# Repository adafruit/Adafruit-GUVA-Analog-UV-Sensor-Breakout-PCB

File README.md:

# Adafruit-GUVA-Analog-UV-Sensor-Breakout-PCB

__Format is EagleCAD schematic and board layout__

<a href="http://www.adafruit.com/products/1918"><br/>Click here to purchase one from the Adafruit shop</a>

Extend your light-sensing spectrum with this analog UV sensor module. It uses a UV photodiode, which can detect the 240-370nm range of light (which covers UVB and most of UVA spectrum). The signal level from the photodiode is very small, in the nano-ampere level, so we tossed on an opamp to amplify the signal to a more manageable volt-level.

This sensor is much simpler than our Si1145 breakout, it only does one thing and gives an analog voltage output instead of requiring a complicated I2C setup procedure. This makes it better for simple projects. It also has a 'true' UV sensor instead of a calibrated light-sensor. To use, power the sensor and op-amp by connecting V+ to 2.7-5.5VDC and GND to power ground. Then read the analog signal from the OUT pin. The output voltage is: Vo = 4.3 * Diode-Current-in-uA. So if the photocurrent is 1uA (9 mW/cm^2), the output voltage is 4.3V. You can also convert the voltage to UV Index by dividing the output voltage by 0.1V. So if the output voltage is 0.5V, the UV Index is about 5.

Please note, our UV LEDs are 400nm, outside the range of this sensor, so if you're trying to test this sensor, don't use them! A UV tanning lamp or 'lizard-lamp' will work much better.

## License

Adafruit invests time and resources providing this open source design, 
please support Adafruit and open-source hardware by purchasing 
products from Adafruit!

Designed by Adafruit Industries.  
Creative Commons Attribution, Share-Alike license, check license.txt for more information
All text above must be included in any redistribution

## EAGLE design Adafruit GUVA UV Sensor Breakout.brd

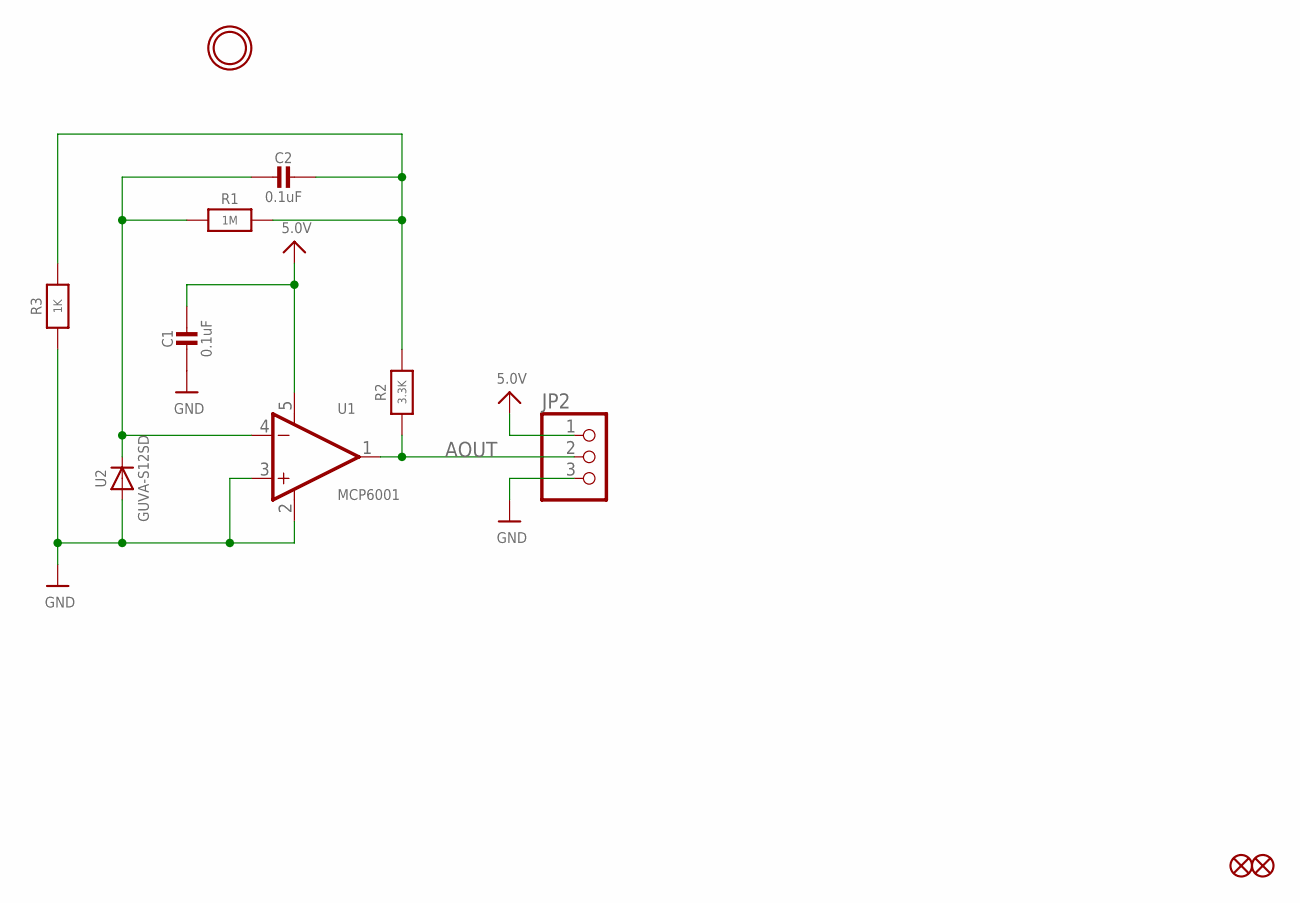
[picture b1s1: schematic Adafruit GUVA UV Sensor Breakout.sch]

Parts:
C1, C2: 0.1uF; 0805-NO
FID1, FID2: FIDUCIAL""; FIDUCIAL_1MM
JP2: PINHD-1X3CB; 1X03-CLEANBIG
R1: 1M; 0805-NO
R2: 3.3K; 0805-NO
R3: 1K; 0805-NO
U1: MCP6001; SOT23-5
U2: GUVA-S12SD
U$6: MOUNTINGHOLE2.5; MOUNTINGHOLE_2.5_PLATED

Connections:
5.0V: C1.1, JP2.1, U1.5 (V+)
AOUT: JP2.2, R2.1, U1.1 (OUT)
GND: C1.2, JP2.3, R3.1, U1.2 (V-), U1.3 (+IN), U2.A
unnamed: C2.1, R1.2, R2.2, R3.2
unnamed: C2.2, R1.1, U1.4 (-IN), U2.K (C)

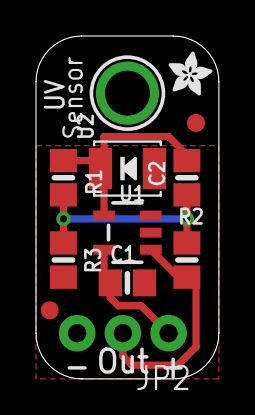
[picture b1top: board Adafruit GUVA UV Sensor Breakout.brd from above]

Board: 2 copper layers, 10.2 x 19.1 mm, 13 parts (1 on the bottom side), 5 nets.

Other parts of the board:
U$7, U$8: ADAFRUIT_2.5MM

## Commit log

2016-06-06 init!
2019-06-14 readme + image + license

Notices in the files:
parts and their libraries:
microbuilder: This work is placed in the public domain, and may be freely used for commercial and non-commercial work with the following conditions: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
